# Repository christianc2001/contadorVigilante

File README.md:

# Sistema de detección de apertura de contadores de agua/gas

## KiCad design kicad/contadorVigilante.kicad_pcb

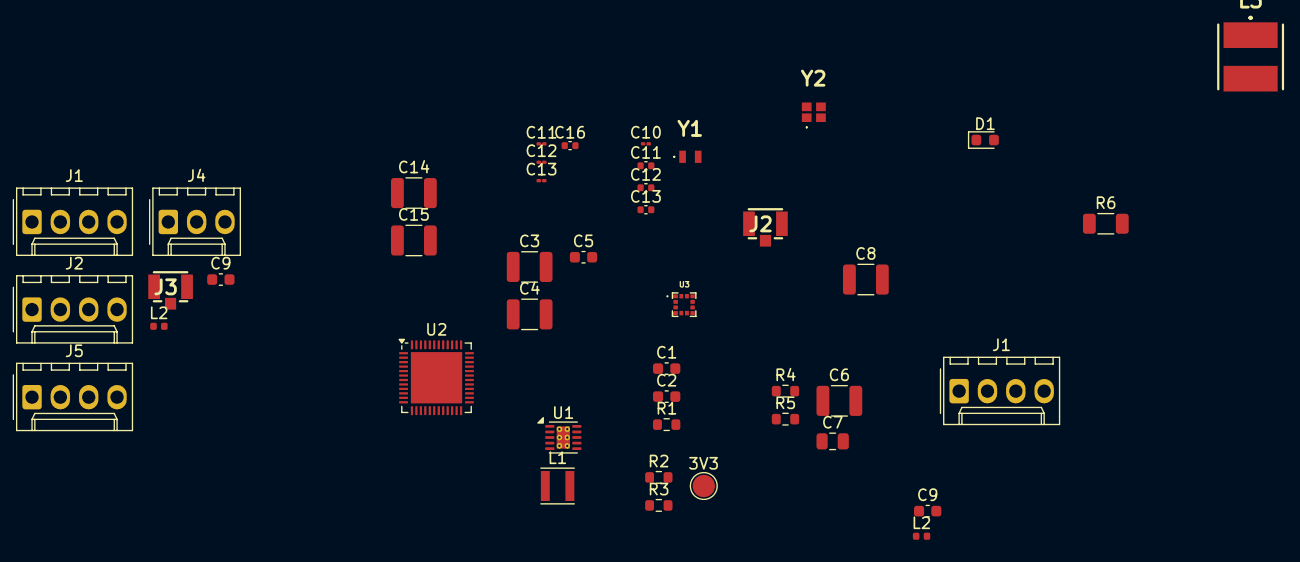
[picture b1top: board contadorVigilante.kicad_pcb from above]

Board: 2 copper layers, 44 parts (0 on the bottom side), 35 nets, no tracks yet.

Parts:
3V3: TestPoint_Pad_D2.0mm
C1: 10uF; C_0603_1608Metric
C2: 22uF; C_0603_1608Metric
C3, C4, C6, C8, C14, C15: 100nF; C_1210_3225Metric
C5: 4.7uF; C_0603_1608Metric
C7: 10uF; C_0805_2012Metric
C9, C9#2: 0.8pF; C_0603_1608Metric
C10, C11#2, C12#2, C13#2: 12pF; C_01005_0402Metric
C11, C12, C13: 12pF; C_0402_1005Metric
C16: 1uF; C_0402_1005Metric
D1: LED; LED_0603_1608Metric
J1, J1#2, J2, J5: Conn_01x04_Pin; Molex_KK-254_AE-6410-04A_1x04_P2.54mm_Vertical
J2#2, J3: 1909763-1
J4: Conn_01x03_Pin; Molex_KK-254_AE-6410-03A_1x03_P2.54mm_Vertical
L1: 2.2uH; L_Taiyo-Yuden_MD-3030
L2, L2#2: 3.9nH; L_0402_1005Metric
L3: 10uH; SRR5828A2R6Y
R1: 36.5kOhm; R_0603_1608Metric
R2, R3, R4, R5: 0Ohm; R_0603_1608Metric
R6: 1kOhm; C_1206_3216Metric
U1: TPS63900; WSON-10-1EP_2.5x2.5mm_P0.5mm_EP1.2x2mm_ThermalVias
U2: nRF52832-QFxx; QFN-48-1EP_6x6mm_P0.4mm_EP4.6x4.6mm
U3: LIS2DW12TR; LGA12R50P4X4_200X200X70
Y1: 32.768kHz; 830050789
Y2: 32MHz; 830108212909

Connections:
+3V3: 3V3.1, C2.1, C3.1, C4.1, C5.1, J1#2.1, J2.1, R4.1, U1.6 (VOUT), U2.13 (VDD), U2.36 (VDD), U2.48 (VDD)
/DEC4: C16.1, U2.46 (DEC4)
ADC0: J5.1, U2.4 (P0.02/AIN0)
ADC1: J5.2, U2.5 (P0.03/AIN1)
ADC2: J5.3, U2.6 (P0.04/AIN2)
ADC3: J5.4, U2.7 (P0.05/AIN3)
ANT: C9.1, C9#2.1, L2.2, L2#2.2, U2.30 (ANT)
GND: C1.2, C2.2, C3.2, C4.2, C5.2, C6.2, C7.2, C8.2, C9.2, C9#2.2, C10.2, C11.2, C11#2.2, C12.1, C12#2.1, C13.1, C13#2.1, C14.2, C15.2, C16.2, D1.1 (K), J1#2.4, J2.4, J2#2.2, J2#2.3, J3.2, J3.3, J4.3, R1.2, R2.2, R3.2, U1.8 (GND), U1.11 (GND), U2.31 (VSS), U2.45 (VSS), U2.49 (VSS), U3.6 (GND), U3.7 (RES), U3.8 (GND)
unnamed: D1.2 (A), R6.2
unnamed: J2#2.1, L2#2.1
unnamed: J3.1, L2.1
unnamed: R1.1, U1.3 (CFG1)
unnamed: R2.1, U1.4 (CFG2)
unnamed: R3.1, U1.5 (CFG3)
unnamed: L1.1, U1.9 (LX1)
unnamed: L1.2, U1.7 (LX2)
unnamed: L3.1, U2.47 (DCC)
unnamed: C14.1, U2.1 (DEC1)
unnamed: C15.1, U2.33 (DEC3)
unnamed: C10.1, U2.2 (P0.00/XL1), Y1.1
unnamed: C11.1, C11#2.1, U2.3 (P0.01/XL2), Y1.2
unnamed: R6.1, U2.10 (P0.08)
unnamed: C12.2, C12#2.2, U2.34 (XC1), Y2.1
unnamed: C13.2, C13#2.2, U2.35 (XC2), Y2.2
unnamed: R5.1, U3.2 (CS)
unnamed: C6.1, C7.1, C8.1, R4.2, R5.2, U3.9 (VDD), U3.10 (VDD_IO)
PIN0: J1.1, U2.14 (P0.11)
PIN1: J1.2, U2.15 (P0.12)
PIN2: J1.3, U2.16 (P0.13)
PIN3: J1.4, U2.17 (P0.14)
RX: J4.1, U2.8 (P0.06)
SWDCLK: J1#2.2, J2.2, U2.25 (SWDCLK)
SWDIO: J1#2.3, J2.3, U2.26 (SWDIO)
TX: J4.2, U2.9 (P0.07)
VIN: C1.1, U1.1 (EN), U1.2 (SEL), U1.10 (VIN)

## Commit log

2024-09-04 Archivos principales v1
